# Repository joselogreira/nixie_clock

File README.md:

# **The Nixie Tube Clock** by [Nuvitron]

![alt text][clock_pcb]

At Nuvitron, I led the electronics development of The Nixie Clock hardware included in some of their models. This repository starts from the production version of the clock circuit, and includes further improvements in the form of:

- Code refactoring
- Hardware tweaks (pending)

---

## Toolchain:

This project is based on an [ATmega324pb][324pb] MCU from Atmel (now Microchip). The standard AVR toolchain for Ubuntu Linux was used. No bootloader implemented. Not tested under Windows or Mac.

- [avr-gcc] for compiling and building.
- [avr-libc] for AVR libraries.
- [avrdude] for programming, using [usbasp] programmer or alternatively the official [AVR ISP MK2][mk2]

There're many guides on how to install and set-up the toolchain. [Here's one] of many guides available.

***Sidenote:*** The ATmega324pb MCU is NOT supported by default, neither by *AVRdude* nor by *avr-gcc*, thus, a few extra steps need to be performed in order to get this toolchain to work properly. It's just a matter of including some extra files in the proper locatios to fully support the MCU:
* **AVRdude**: it uses a configuration file that includes all MCUs recognized by the program, among other things. Mine is at `/etc/avrdude.conf`. Edit it (with *root* proviledges) and add an entry for the *ATmega324pb*. Use the *ATmega324pa* as an example, which inherits most of the properties from the ATmega324p. The signature for the 324pb is `1e 95 17`. Alternatively, I've added my `avrdude.conf` to the repo, [here][special].
* **avr-gcc**: A device specification file must be included. My path: `/usr/lib/gcc/avr/5.4.0/device-spec/`. The missing file is called `specs-atmega324pb` and I found it in a Windows installation of [Atmel Studio][astudio], the Atmel IDE for Windows. Within this file there's a couple of dependencies pointing to files in the avr-libc path.
* **avr-libc**: Three files are needed. Again, I found them in the Atmel Studio Windows installation path. My paths for these files are:
  * `/usr/lib/avr/include/avr/` must include the file `iom324pb.h`, which is the memory mapping for all MCU peripherals and special registers.
  * `/usr/lib/avr/lib/avr5/` must include `crtatmega324pb.o` and `libatmega324pb.a`.

***Sidenote 2:*** The latest version of Atmel Studio (7.0, at the time of this writting) doesn't include support for the *ATmega324pb* out-of-the-box. Instead, the user must install an additional package to fully support it. It's called *"Device Firmware Pack"*, and it's installed within Atmel Studio in the *"Device Package Manager"* window. Search for ATmega_DFP and install it. Mine was version `1.2.272`. Once installed, the previously mentioned Windows files can be found at:
  * `\<install-path>\Atmel\Studio\7.0\packs\atmel\ATmega_DFP\1.2.272\include\avr\iom324pb.h`
  * `\<install-path>\Atmel\Studio\7.0\packs\atmel\ATmega_DFP\1.2.272\gcc\dev\atmega324pb\avr5\crtatmega324pb.o` and `libatmega324pb.a`
  * `\<install-path>\Atmel\Studio\7.0\packs\atmel\ATmega_DFP\1.2.272\gcc\dev\atmega324pb\device-specs\specs-atmega324pb`

For the sake of completeness, these files are also included [here][special].

---

## Project Folders
- **src**: contains all the code files needed, including library files.
- **special**: contains all *"additional"* files to support the MCU.
- **img**: some images of the project.
- **docs**: GitHub [project page][ppage].
- **output**: not included in the repo. Automatically created once the Make recipe is executed.

---

## Hardware Characteristics:
- MCU: ATmega324pb 
- (pending)

---

## License

Released under the [MIT License][license] - 2020 Jose Logreira

[clock_pcb]: https://raw.githubusercontent.com/joselogreira/nixie_clock/master/img/clock_pcb.png "Nixie Clock Circuit"
[Nuvitron]: <https://nuvitron.com>
[avr-gcc]: <https://www.microchip.com/mplab/avr-support/avr-and-arm-toolchains-c-compilers>
[avr-libc]: <https://www.nongnu.org/avr-libc/user-manual/overview.html>
[avrdude]: <https://www.nongnu.org/avrdude/>
[usbasp]: <https://www.fischl.de/usbasp/>
[Here's one]: <http://maxembedded.com/2015/06/setting-up-avr-gcc-toolchain-on-linux-and-mac-os-x/>
[special]: /special/
[astudio]: https://www.microchip.com/mplab/avr-support/atmel-studio-7
[324pb]: http://ww1.microchip.com/downloads/en/DeviceDoc/40001908A.pdf
[mk2]: http://ww1.microchip.com/downloads/en/DeviceDoc/Atmel-42093-AVR-ISP-mkII_UserGuide.pdf
[license]: /LICENSE
[ppage]: https://joselogreira.github.io/nixie_clock/

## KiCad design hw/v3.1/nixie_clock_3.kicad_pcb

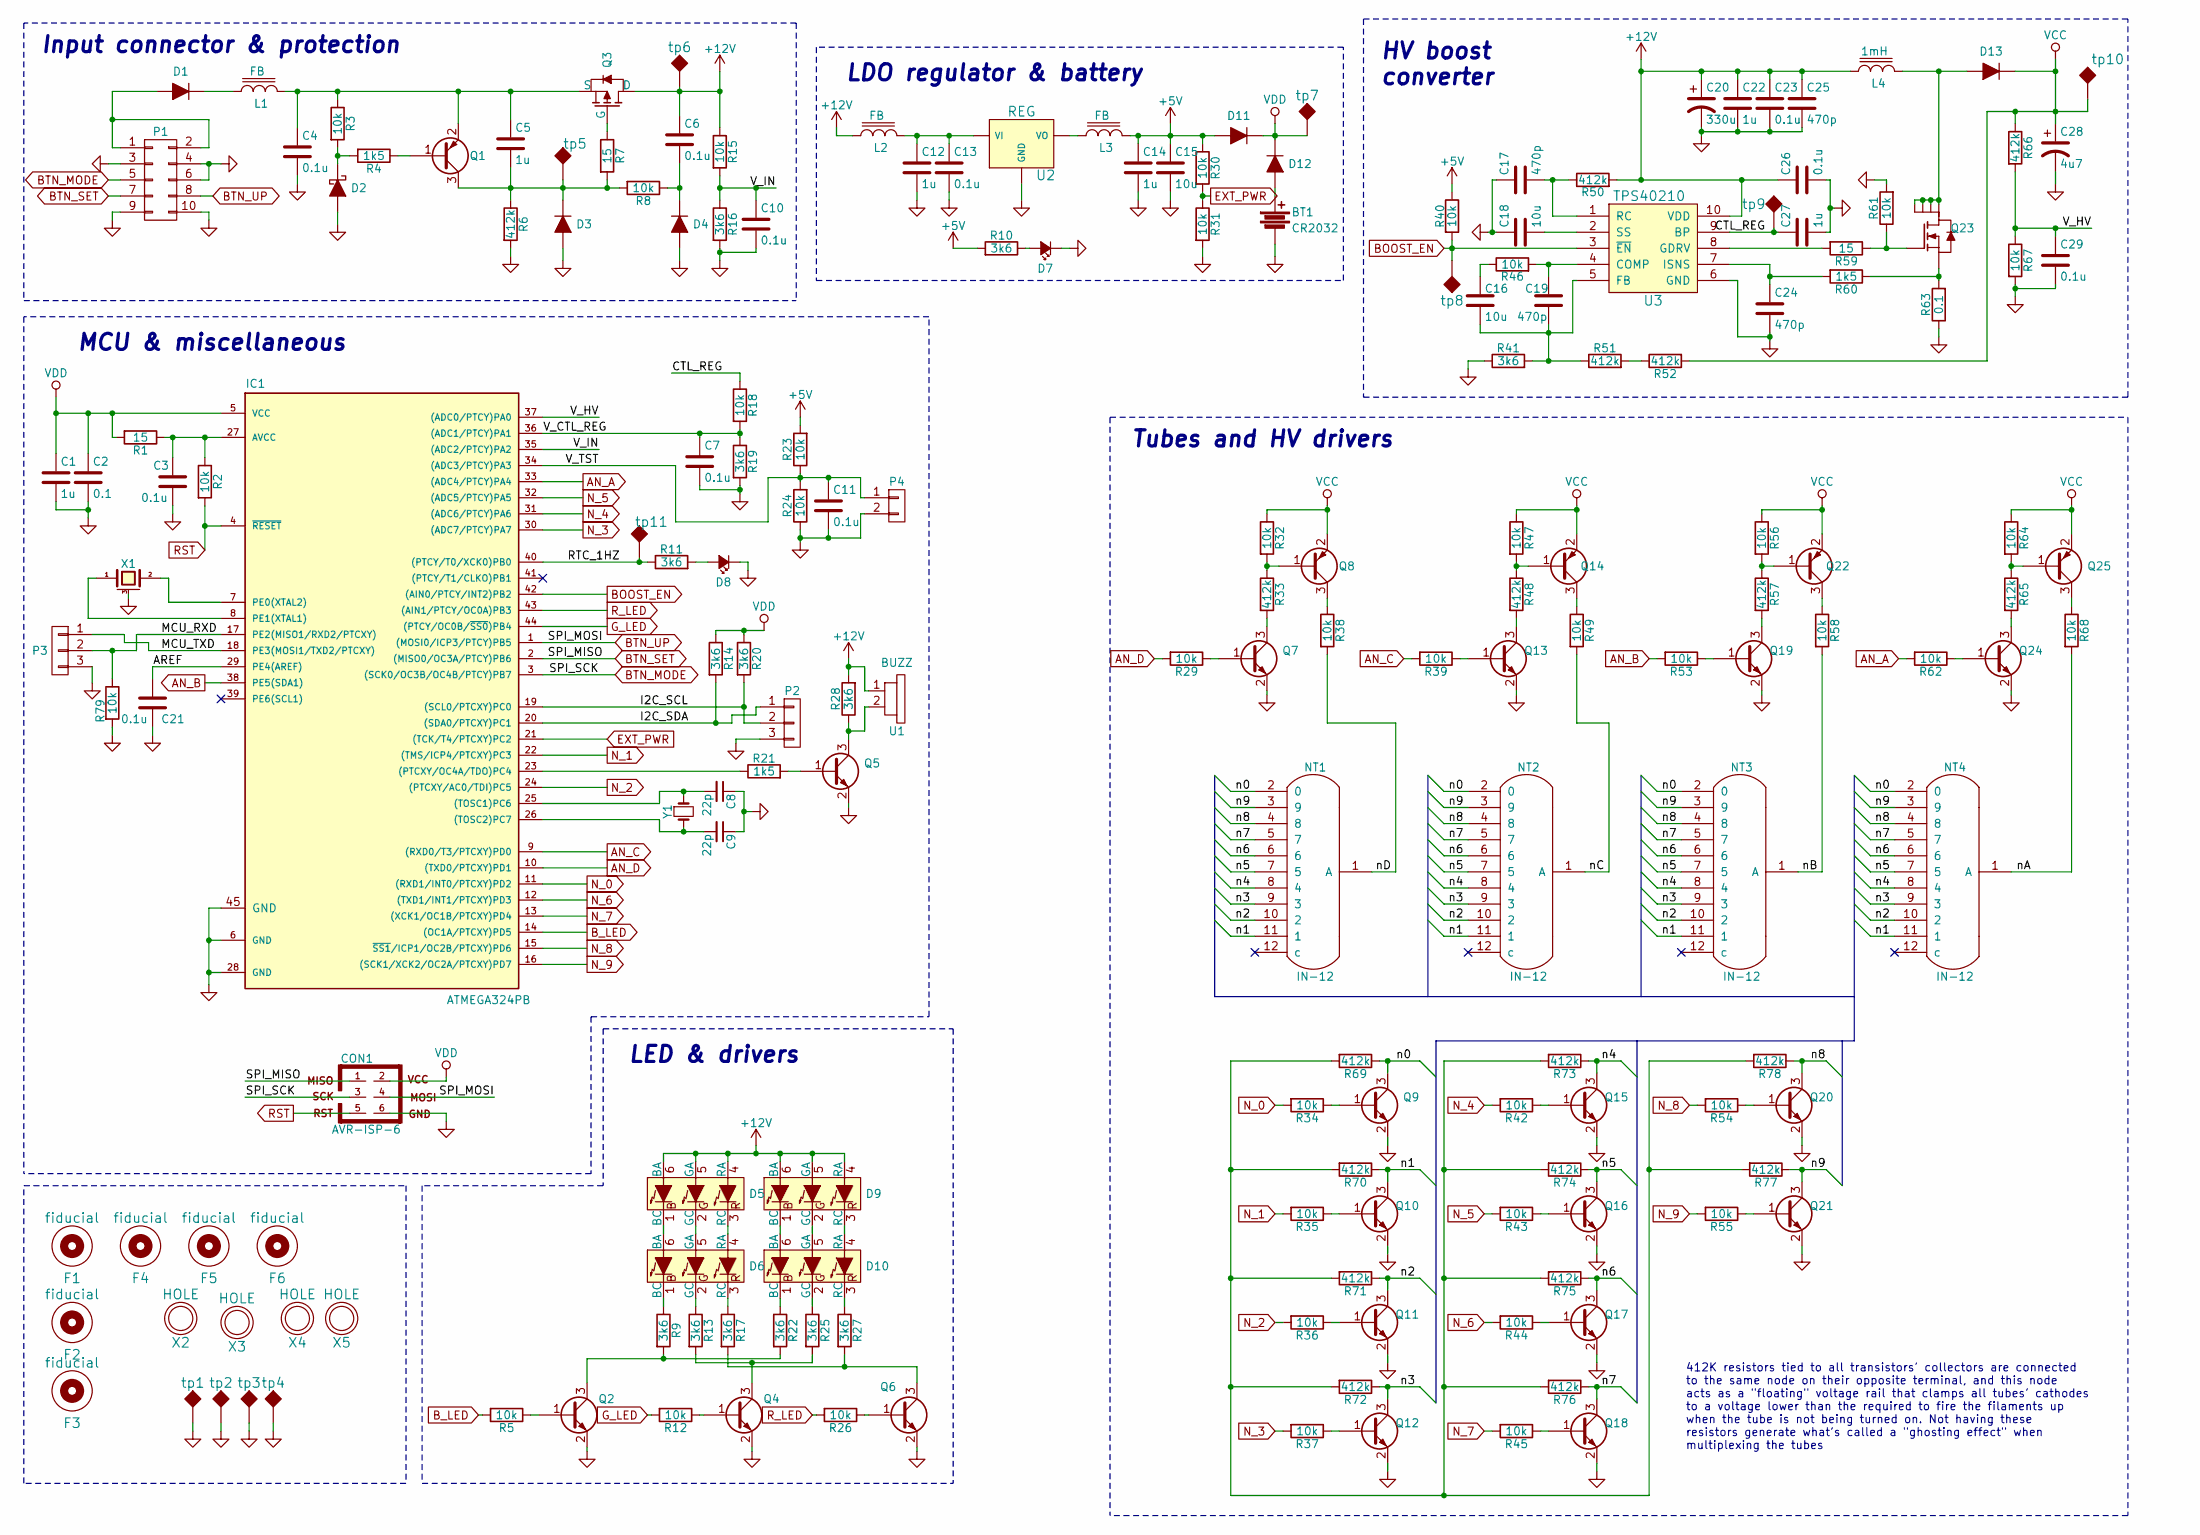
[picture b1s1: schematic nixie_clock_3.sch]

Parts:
BT1: CR2032
C1, C5, C12, C14, C22, C27: 1u; C_0603
C2: 0.1; C_0603
C3, C4, C6, C7, C10, C11, C13, C21, C23, C26, C29: 0.1u; C_0603
C8, C9: 22p; C_0603
C15, C16, C18: 10u; C_0805
C17, C19, C24, C25: 470p; C_0603
C20: 330u; CP_Elec_8x10
C28: 4u7; CP_Elec_8x10
CON1: AVR-ISP-6; ISP_THT_UNPOPULATED
D1, D13: D_ALT; DO-214AC
D2: D_Schottky_ALT; SOD-323
D3, D4, D11, D12: D_ALT; SOD-323
D5, D6, D9, D10: LED_RGB_IND; LED_RGB_PLCC-6-SMALL
D7, D8: Led_Small; D_0603
F1, F2, F3, F4, F5, F6: fiducial; Fiducial_1mm_Dia_2.54mm_Outer_CopperTop
IC1: ATMEGA324PB; QFN-44-1EP_7x7mm_Pitch0.5mm
L1, L2, L3: FB; C_0603
L4: 1mH; IND_1MH_7.3x7.3mm
NT1, NT2, NT3, NT4: IN-12
P1: CONN_02X05; CON_2x5
P2, P3: CONN_01X03; CON_1x3
P4: CONN_01X02; CON_1x2
Q1, Q8, Q14, Q22, Q25: Q_PNP_BEC; SOT-23
Q2, Q4, Q5, Q6, Q7, Q9, Q10, Q11, Q12, Q13, Q15, Q16, Q17, Q18, Q19, Q20, Q21, Q24: Q_NPN_BEC; SOT-23
Q3: Q_PMOS_GSD_; SOT-23
Q23: Q_NMOS_GSD_6; SOT-23-6
R1, R7, R59: 15; C_0603
R2, R3, R5, R8, R12, R15, R18, R23, R24, R26, R29, R30, R31, R32, R34, R35, R36, R37, R38, R39, R40, R42, R43, R44, R45, R46, R47, R49, R53, R54, R55, R56, R58, R61, R62, R64, R67, R68, R79: 10k; C_0603
R4, R21, R60: 1k5; C_0603
R6, R33, R48, R50, R51, R52, R57, R65, R66, R69, R70, R71, R72, R73, R74, R75, R76, R77, R78: 412k; C_0805
R9, R10, R11, R13, R14, R16, R17, R19, R20, R22, R25, R27, R28, R41: 3k6; C_0603
R63: 0.1; C_0603
U1: BUZZ; BUZZ-D12,6_P5
U2: REG; SOT-223
U3: TPS40210; 10-MSOP
X1: CRYSTAL_SMD; CERAMIC_RESONATOR
X2, X3, X4, X5: HOLE; MOUNTING_NPTH_3.2MM
Y1: Crystal_Small; Crystal_3.2x1.5mm
tp1, tp2, tp3, tp4: tp; TestPoint_Pad_3.0x3.0mm
tp5, tp6, tp7, tp8, tp9, tp10, tp11: tp

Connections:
+5V: C14.1, C15.1, D11.2 (A), L3.1, R10.2, R23.2, R30.1, R40.1
+12V: C6.1, C20.1, C22.1, C23.1, C25.1, C26.1, D5.4 (RA), D5.5 (GA), D5.6 (BA), D9.4 (RA), D9.5 (GA), D9.6 (BA), L2.2, L4.2, Q3.3 (D), R15.1, R28.2, R50.2, U1.1, U3.10 (VDD), tp6.1
/AREF: C21.1, IC1.29 (PE4(AREF))
/CTL_REG: C27.1, R18.1, U3.9 (BP), tp9.1
/I2C_SCL: IC1.19 ((SCL0/PTCXY)PC0), P2.2, R20.2
/I2C_SDA: IC1.20 ((SDA0/PTCXY)PC1), P2.1, R14.2
/MCU_RXD: IC1.17 (PE2(MISO1/RXD2/PTCXY)), P3.2, R79.1
/MCU_TXD: IC1.18 (PE3(MOSI1/TXD2/PTCXY)), P3.1
/RTC_1HZ: IC1.40 ((PTCY/T0/XCK0)PB0), R11.1, tp11.1
/V_CTL_REG: C7.1, IC1.36 ((ADC1/PTCY)PA1), R18.2, R19.1
/V_HV: C29.1, IC1.37 ((ADC0/PTCY)PA0), R66.2, R67.1
/V_IN: C10.1, IC1.35 ((ADC2/PTCY)PA2), R15.2, R16.1
/V_TST: C11.1, IC1.34 ((ADC3/PTCY)PA3), P4.1, R23.1, R24.2
/n0: NT1.2 (0), NT2.2 (0), NT3.2 (0), NT4.2 (0), Q9.3 (C), R69.1
/n1: NT1.11 (1), NT2.11 (1), NT3.11 (1), NT4.11 (1), Q10.3 (C), R70.1
/n2: NT1.10 (2), NT2.10 (2), NT3.10 (2), NT4.10 (2), Q11.3 (C), R71.1
/n3: NT1.9 (3), NT2.9 (3), NT3.9 (3), NT4.9 (3), Q12.3 (C), R72.1
/n4: NT1.8 (4), NT2.8 (4), NT3.8 (4), NT4.8 (4), Q15.3 (C), R73.1
/n5: NT1.7 (5), NT2.7 (5), NT3.7 (5), NT4.7 (5), Q16.3 (C), R74.1
/n6: NT1.6, NT2.6, NT3.6, NT4.6, Q17.3 (C), R75.1
/n7: NT1.5 (7), NT2.5 (7), NT3.5 (7), NT4.5 (7), Q18.3 (C), R76.1
/n8: NT1.4 (8), NT2.4 (8), NT3.4 (8), NT4.4 (8), Q20.3 (C), R78.1
/n9: NT1.3 (9), NT2.3 (9), NT3.3 (9), NT4.3 (9), Q21.3 (C), R77.1
/nA: NT4.1 (A), R68.2
/nB: NT3.1 (A), R58.2
/nC: NT2.1 (A), R49.2
/nD: NT1.1 (A), R38.2
AN_A: IC1.33 ((ADC4/PTCY)PA4), R62.2
AN_B: IC1.38 (PE5(SDA1)), R53.2
AN_C: IC1.9 ((RXD0/T3/PTCXY)PD0), R39.2
AN_D: IC1.10 ((TXD0/PTCXY)PD1), R29.2
BOOST_EN: IC1.42 ((AIN0/PTCY/INT2)PB2), R40.2, U3.3 (~EN), tp8.1
BTN_MODE: CON1.3, IC1.3 ((SCK0/OC3B/OC4B/PTCY)PB7), P1.5
BTN_SET: CON1.1, IC1.2 ((MISO0/OC3A/PTCY)PB6), P1.7
BTN_UP: CON1.4, IC1.1 ((MOSI0/ICP3/PTCY)PB5), P1.8
B_LED: IC1.14 ((OC1A/PTCXY)PD5), R5.2
EXT_PWR: IC1.21 ((TCK/T4/PTCXY)PC2), R30.2, R31.1
GND: BT1.2, C1.2, C2.2, C3.2, C4.2, C7.2, C8.1, C9.1, C10.2, C11.2, C12.2, C13.2, C14.2, C15.2, C17.1, C18.1, C20.2, C21.2, C22.2, C23.2, C24.2, C25.2, C26.2, C27.2, C28.2, C29.2, CON1.6, D2.2 (A), D3.2 (A), D4.2 (A), D7.1 (K), D8.1 (K), IC1.6 (GND), IC1.28 (GND), IC1.45 (GND), P1.3, P1.4, P1.6, P1.9, P1.10, P2.3, P3.3, P4.2, Q2.2 (E), Q4.2 (E), Q5.2 (E), Q6.2 (E), Q7.2 (E), Q9.2 (E), Q10.2 (E), Q11.2 (E), Q12.2 (E), Q13.2 (E), Q15.2 (E), Q16.2 (E), Q17.2 (E), Q18.2 (E), Q19.2 (E), Q20.2 (E), Q21.2 (E), Q24.2 (E), R6.2, R16.2, R19.2, R24.1, R31.2, R41.1, R61.2, R63.1, R67.2, R79.2, U2.1 (GND), U3.6 (GND), X1.3 (case), tp1.1, tp2.1, tp3.1, tp4.1
G_LED: IC1.44 ((PTCY/OC0B/~SS0~)PB4), R12.2
N_0: IC1.11 ((RXD1/INT0/PTCXY)PD2), R34.2
N_1: IC1.22 ((TMS/ICP4/PTCXY)PC3), R35.2
N_2: IC1.24 ((PTCXY/AC0/TDI)PC5), R36.2
N_3: IC1.30 ((ADC7/PTCY)PA7), R37.2
N_4: IC1.31 ((ADC6/PTCY)PA6), R42.2
N_5: IC1.32 ((ADC5/PTCY)PA5), R43.2
N_6: IC1.12 ((TXD1/INT1/PTCXY)PD3), R44.2
N_7: IC1.13 ((XCK1/OC1B/PTCXY)PD4), R45.2
N_8: IC1.15 (~SS1~/ICP1/OC2B/PTCXY)PD6), R54.2
N_9: IC1.16 ((SCK1/XCK2/OC2A/PTCXY)PD7), R55.2
unnamed: BT1.1, D12.2 (A)
unnamed: C3.1, IC1.27 (AVCC), R1.1, R2.1
unnamed: C4.1, C5.1, L1.1, Q1.2 (E), Q3.2 (S), R3.1
unnamed: C5.2, D3.1 (K), Q1.3 (C), R6.1, R7.2, R8.2, tp5.1
unnamed: C6.2, D4.1 (K), R8.1
unnamed: C8.2, IC1.25 ((TOSC1)PC6), Y1.1
unnamed: C9.2, IC1.26 ((TOSC2)PC7), Y1.2
unnamed: C12.1, C13.1, L2.1, U2.3 (VI)
unnamed: C16.1, R46.1
unnamed: C16.2, C19.2, R41.2, R51.1, U3.5 (FB)
unnamed: C17.2, R50.1, U3.1 (RC)
unnamed: C18.2, U3.2 (SS)
unnamed: C19.1, R46.2, U3.4 (COMP)
unnamed: C24.1, R60.2, U3.7 (ISNS)
unnamed: D1.1 (K), L1.2
unnamed: D1.2 (A), P1.1, P1.2
unnamed: D2.1 (K), R3.2, R4.2
unnamed: D5.1 (BC), D6.6 (BA)
unnamed: D5.2 (GC), D6.5 (GA)
unnamed: D5.3 (RC), D6.4 (RA)
unnamed: D6.1 (BC), R9.1
unnamed: D6.2 (GC), R13.1
unnamed: D6.3 (RC), R17.1
unnamed: D7.2 (A), R10.1
unnamed: D8.2 (A), R11.2
unnamed: D10.1 (BC), R22.1
unnamed: D10.2 (GC), R25.1
unnamed: D10.3 (RC), R27.1
unnamed: D9.3 (RC), D10.4 (RA)
unnamed: D9.2 (GC), D10.5 (GA)
unnamed: D9.1 (BC), D10.6 (BA)
unnamed: D13.2 (A), L4.1, Q23.1, Q23.2 (D), Q23.5, Q23.6
unnamed: IC1.7 (PE0(XTAL2)), X1.2
unnamed: IC1.8 (PE1(XTAL1)), X1.1
unnamed: IC1.23 ((PTCXY/OC4A/TDO)PC4), R21.1
unnamed: L3.2, U2.2 (VO)
unnamed: Q1.1 (B), R4.1
unnamed: Q2.1 (B), R5.1
unnamed: Q2.3 (C), R9.2, R22.2
unnamed: Q3.1 (G), R7.1
unnamed: Q4.1 (B), R12.1
unnamed: Q4.3 (C), R13.2, R25.2
unnamed: Q5.1 (B), R21.2
unnamed: Q5.3 (C), R28.1, U1.2
unnamed: Q6.1 (B), R26.1
unnamed: Q6.3 (C), R17.2, R27.2
unnamed: Q7.1 (B), R29.1
unnamed: Q7.3 (C), R33.2
unnamed: Q8.1 (B), R32.2, R33.1
unnamed: Q8.3 (C), R38.1
unnamed: Q9.1 (B), R34.1
unnamed: Q10.1 (B), R35.1
unnamed: Q11.1 (B), R36.1
unnamed: Q12.1 (B), R37.1
unnamed: Q13.1 (B), R39.1
unnamed: Q13.3 (C), R48.2
unnamed: Q14.1 (B), R47.2, R48.1
unnamed: Q14.3 (C), R49.1
unnamed: Q15.1 (B), R42.1
unnamed: Q16.1 (B), R43.1
unnamed: Q17.1 (B), R44.1
unnamed: Q18.1 (B), R45.1
unnamed: Q19.1 (B), R53.1
unnamed: Q19.3 (C), R57.2
unnamed: Q20.1 (B), R54.1
unnamed: Q21.1 (B), R55.1
unnamed: Q22.1 (B), R56.2, R57.1
unnamed: Q22.3 (C), R58.1
unnamed: Q23.3 (G), R59.1, R61.1
unnamed: Q23.4 (S), R60.1, R63.2
unnamed: Q24.1 (B), R62.1
unnamed: Q24.3 (C), R65.2
unnamed: Q25.1 (B), R64.2, R65.1
unnamed: Q25.3 (C), R68.1
unnamed: R51.2, R52.1
unnamed: R59.2, U3.8 (GDRV)
unnamed: R69.2, R70.2, R71.2, R72.2, R73.2, R74.2, R75.2, R76.2, R77.2, R78.2
RST: CON1.5, IC1.4 (~RESET), R2.2
R_LED: IC1.43 ((AIN1/PTCY/OC0A)PB3), R26.2
VCC: C28.1, D13.1 (K), Q8.2 (E), Q14.2 (E), Q22.2 (E), Q25.2 (E), R32.1, R47.1, R52.2, R56.1, R64.1, R66.1, tp10.1
VDD: C1.1, C2.1, CON1.2, D11.1 (K), D12.1 (K), IC1.5 (VCC), R1.2, R14.1, R20.1, tp7.1

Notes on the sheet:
Input connector & protection
MCU & miscellaneous
HV boost converter
LDO regulator & battery
Tubes and HV drivers
LED & drivers
412K resistors tied to all transistors' collectors are connected to the same node on their opposite terminal, and this node acts as a "floating" voltage rail that clamps all tubes' cathodes to a voltage lower than the required to fire the filaments up when the tube is not being turned on. Not havin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

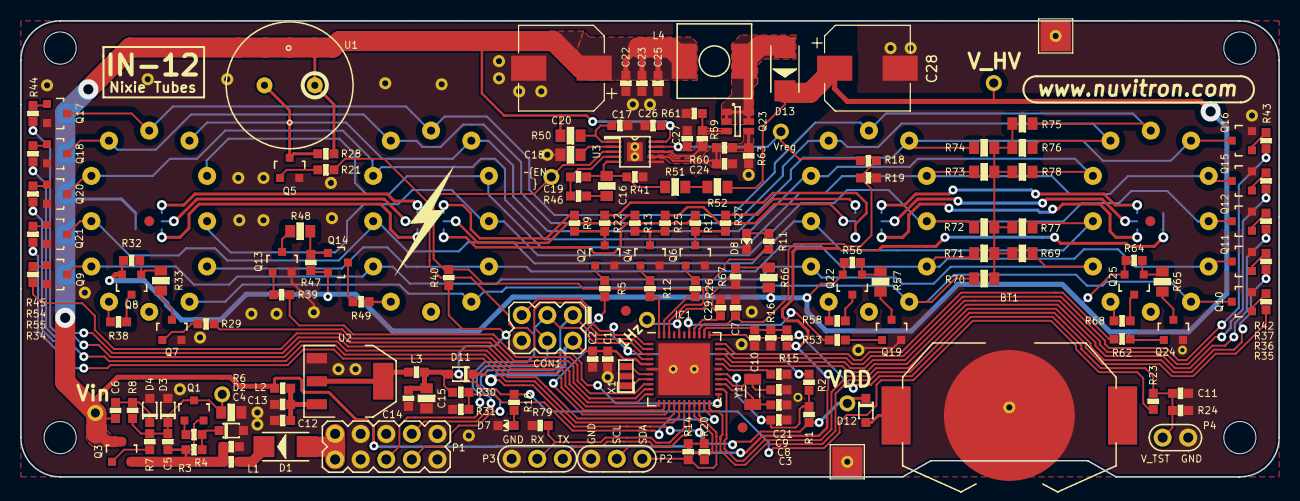
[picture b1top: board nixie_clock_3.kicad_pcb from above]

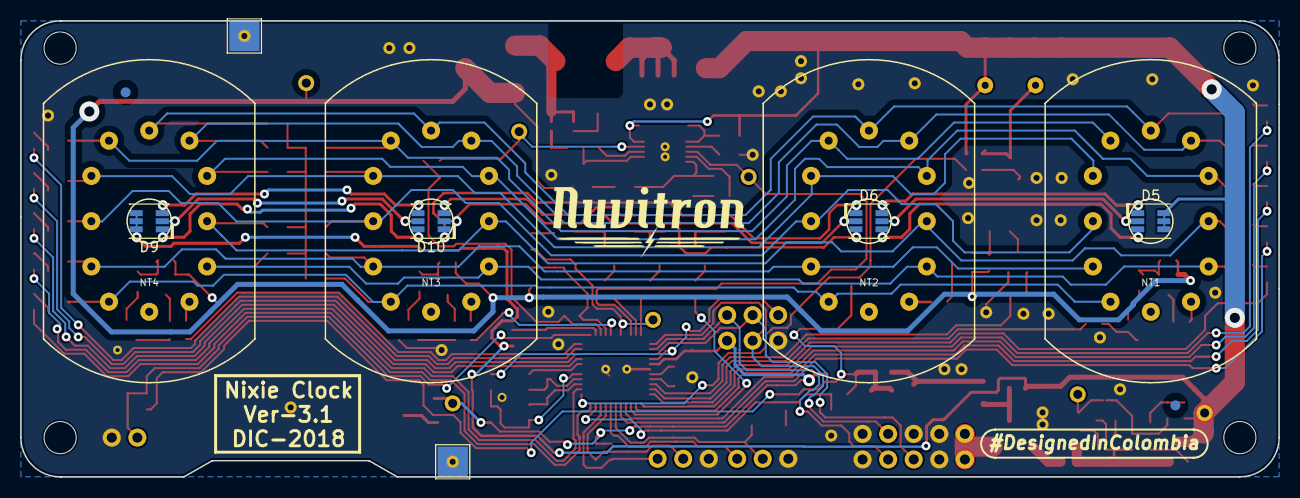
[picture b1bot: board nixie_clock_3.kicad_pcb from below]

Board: 2 copper layers, 125.0 x 45.3 mm, 187 parts (12 on the bottom side), 130 nets.

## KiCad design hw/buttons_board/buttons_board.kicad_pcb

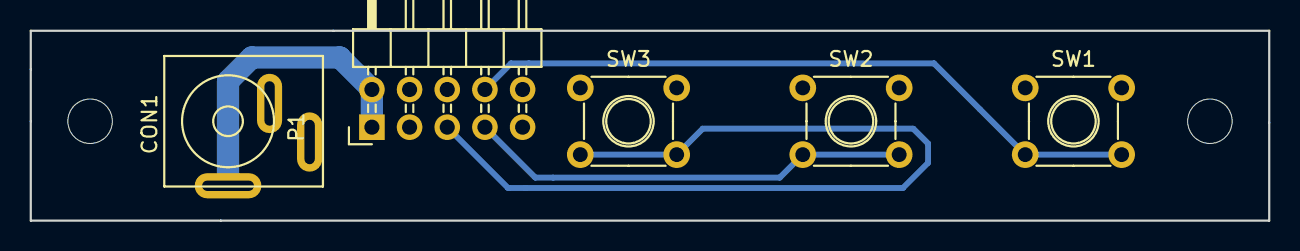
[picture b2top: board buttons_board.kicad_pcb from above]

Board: 2 copper layers, 83.5 x 12.8 mm, 7 parts (0 on the bottom side), 5 nets.

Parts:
CON1: BARREL_JACK; CON_PWR_JACK_5.5x2mm
P1: CONN_02X05; Pin_Header_Angled_2x05
SW1: UP; SW_SPST_THT_6mm
SW2: SET; SW_SPST_THT_6mm
SW3: MODE; SW_SPST_THT_6mm
X1, X2: HOLE; MountingHole_3-5mm

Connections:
GND: CON1.2, CON1.3, P1.3, P1.4, P1.6, SW1.3, SW1.4, SW2.3, SW2.4, SW3.3, SW3.4
unnamed: CON1.1, P1.1, P1.2
unnamed: P1.5, SW3.1, SW3.2
unnamed: P1.7, SW2.1, SW2.2
unnamed: P1.8, SW1.1, SW1.2

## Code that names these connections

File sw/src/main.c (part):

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
    /*
    * Power source check:
    * Look for EXT_PWR pin. If there's an external power adapter connected,
    * Initialize RTC, enable Boost and all other peripherals. Run system.
    * If no voltage in EXT_PWR, it means that battery has been connected first.
    * In that case, do nothing and go to sleep.
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
    /*
    * Production Test Enabled?
    * Use the ADC to sense the V_TST pin. If it is short-circuited, it means
    * that the production test must be launched, and a serial communication
    * link will be estabished with a PC using the UART.
    */
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* adapter connection.
* - When buttons are pressed, btnXYZ.query flag is set and the buttons are
*   polled to determine its state.
* - When EXT_PWR pin triggers the ISR, the power adapter was either removed
*   or plugged. Thus, check EXT_PWR level and decide whether going to sleep
*   or keep normal execution.
*/
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/*===========================================================================*/
/* 
* buttons     
* BTN_X       - PB5 - PCINT13 | -> PCI1
* BTN_Y       - PB6 - PCINT14 | -> PCI1
* BTN_Z       - PB7 - PCINT15 | -> PCI1 
*/
ISR(PCINT1_vect)
{
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/* 
* External power
* if external power is removed, enter in power save mode 
* EXT_PWR     - PC2 - PCINT18  | -> PCI2
*/
ISR(PCINT2_vect)
{
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
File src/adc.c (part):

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/* 
* ADC nominal voltages:
*/
#define V_HV  			((float) 3.794)	// nominal 160V
#define V_HV_OFF		((float) 0.273)	// nominal 11.5V
#define V_CTL_REG 		((float) 2.12)	// nominal 8V
#define V_CTL_REG_OFF 	((float) 0.0)	// nominal 0V
#define V_IN 			((float) 3.01)	// nominal 11.4V
#define V_REF 			((float) 1.1)	// nominal 1.1V
#define V_DD 			((float) 4.3)	// nominal MCU voltage v_dd

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
/*===========================================================================*/
/*
* Checks V_TST pin 3 times. If any of the 3 measurements gives a voltage
* greater than (approximately) 0.5V, it returns FALSE.
* In other words, all 3 measurements should be below 0.5V to return TRUE
*/
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		v_ctl_reg.val_min = (uint16_t)(((float)v_ctl_reg.val_nom) * 0.85);
		v_ctl_reg.val_max = (uint16_t)(((float)v_ctl_reg.val_nom) * 1.15);
	} else {
		v_ctl_reg.val_nom = 0;
		v_ctl_reg.val_min = 0;
		v_ctl_reg.val_max = 25;		// 0.1V
	}

	v_in.val_nom = (uint16_t)((V_IN / v_dd) * 1023.0);
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
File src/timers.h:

/**
 * @file timers.h
 * @brief Timer counter configurations
 *
 * @author Jose Logreira
 * @date 15.05.2018
 *
 */

#ifndef TIMERS_H
#define TIMERS_H

/******************************************************************************
*******************	I N C L U D E   D E P E N D E N C I E S	*******************
******************************************************************************/

#include "config.h"

#include <stdint.h>

/******************************************************************************
***************** S T R U C T U R E   D E C L A R A T I O N S *****************
******************************************************************************/

typedef volatile struct {
    uint8_t mode;
    uint8_t d1;
    uint8_t d2;
    uint8_t d3;
    uint8_t d4;
    uint8_t set;
    uint8_t fade_level[4];
} display_s;

extern display_s display;

/******************************************************************************
******************* C O N S T A N T   D E F I N I T I O N S *******************
******************************************************************************/

// LED Register Counters 
#define R_LED			OCR0A
#define G_LED			OCR0B
#define B_LED			OCR1A

/******************************************************************************
******************** F U N C T I O N   P R O T O T Y P E S ********************
******************************************************************************/

void display_init(void);

void timer_rtc_set(uint8_t state);

void timer_base_init(void);
void timer_buzzer_init(void);
void timer_leds_init(void);

void timer_base_set(uint8_t state);
void timer_buzzer_set(uint8_t state, uint16_t note);
void timer_leds_set(uint8_t state, uint8_t r, uint8_t g, uint8_t b);

#endif	/* TIMERS_H */

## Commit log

2020-06-10 First Commit:
    Nuvitron Code - This is the Nuvitron working code. From here, the
    code will be modified/refactored for better presentation
2020-06-10 gitignore new filetypes
2020-06-10 gitignore modified
2020-06-10 Added readme documentation
2020-06-10 readme corrected
2020-06-10 added image
2020-06-10 added image path
2020-06-10 break point for code refactoring
2020-06-10 First round of code refactoring
    Some decissions: Won't change the general code structure.
    It'll remain as-is just to have it as a good future reference.
    Besides, the code is pretty well documented.
2020-06-10 Added Jekyl Project Page Template
2020-06-10 Bump nokogiri from 1.10.5 to 1.10.9 in /docs
    Bumps [nokogiri](https://github.com/sparklemotion/nokogiri) from 1.10.5 to 1.10.9.
    - [Release notes](https://github.com/sparklemotion/nokogiri/releases)
    - [Changelog](https://github.com/sparklemotion/nokogiri/blob/master/CHANGELOG.md)
    - [Commits](https://github.com/sparklemotion/nokogiri/compare/v1.10.5...v1.10.9)
2020-06-10 config.yml changed
2020-06-10 Bump nokogiri from 1.10.5 to 1.10.8 in /docs
    Bumps [nokogiri](https://github.com/sparklemotion/nokogiri) from 1.10.5 to 1.10.8.
    - [Release notes](https://github.com/sparklemotion/nokogiri/releases)
    - [Changelog](https://github.com/sparklemotion/nokogiri/blob/master/CHANGELOG.md)
    - [Commits](https://github.com/sparklemotion/nokogiri/compare/v1.10.5...v1.10.8)
2020-06-11 Main page texts finished
2020-06-11 Getting started added
2020-06-13 By documenting the code base it's notorious that the main loop code is not clear. It's best to include the sei/cli code and buttons routines inside every display state.
    So let's do it from here
2020-06-15 some more code refactoring
2020-06-16 Added documentation, and some code refactoring for buzzer module
2020-06-19 Corrected .h files dependencies
2020-07-01 Added documentation. Added hw designs
2020-07-01 Added YouTube video to Docs pages
2020-07-01 reduced image sizes
2021-05-20 Bump nokogiri from 1.10.9 to 1.11.4 in /docs
    Bumps [nokogiri](https://github.com/sparklemotion/nokogiri) from 1.10.9 to 1.11.4.
    - [Release notes](https://github.com/sparklemotion/nokogiri/releases)
    - [Changelog](https://github.com/sparklemotion/nokogiri/blob/main/CHANGELOG.md)
    - [Commits](https://github.com/sparklemotion/nokogiri/compare/v1.10.9...v1.11.4)
2021-07-13 Bump addressable from 2.7.0 to 2.8.0 in /docs
    Bumps [addressable](https://github.com/sporkmonger/addressable) from 2.7.0 to 2.8.0.
    - [Release notes](https://github.com/sporkmonger/addressable/releases)
    - [Changelog](https://github.com/sporkmonger/addressable/blob/main/CHANGELOG.md)
    - [Commits](https://github.com/sporkmonger/addressable/compare/addressable-2.7.0...addressable-2.8.0)
    ---
    updated-dependencies:
2021-09-28 Bump nokogiri from 1.10.9 to 1.12.5 in /docs
    Bumps [nokogiri](https://github.com/sparklemotion/nokogiri) from 1.10.9 to 1.12.5.
    - [Release notes](https://github.com/sparklemotion/nokogiri/releases)
    - [Changelog](https://github.com/sparklemotion/nokogiri/blob/main/CHANGELOG.md)
    - [Commits](https://github.com/sparklemotion/nokogiri/compare/v1.10.9...v1.12.5)
    ---
    updated-dependencies:
2022-02-26 Bump nokogiri from 1.10.9 to 1.13.2 in /docs
    Bumps [nokogiri](https://github.com/sparklemotion/nokogiri) from 1.10.9 to 1.13.2.
    - [Release notes](https://github.com/sparklemotion/nokogiri/releases)
    - [Changelog](https://github.com/sparklemotion/nokogiri/blob/main/CHANGELOG.md)
    - [Commits](https://github.com/sparklemotion/nokogiri/compare/v1.10.9...v1.13.2)
    ---
    updated-dependencies:
2022-04-12 Bump nokogiri from 1.10.9 to 1.13.4 in /docs
    Bumps [nokogiri](https://github.com/sparklemotion/nokogiri) from 1.10.9 to 1.13.4.
    - [Release notes](https://github.com/sparklemotion/nokogiri/releases)
    - [Changelog](https://github.com/sparklemotion/nokogiri/blob/v1.13.4/CHANGELOG.md)
    - [Commits](https://github.com/sparklemotion/nokogiri/compare/v1.10.9...v1.13.4)
    ---
    updated-dependencies:
2022-05-19 Bump nokogiri from 1.10.9 to 1.13.5 in /docs
    Bumps [nokogiri](https://github.com/sparklemotion/nokogiri) from 1.10.9 to 1.13.5.
    - [Release notes](https://github.com/sparklemotion/nokogiri/releases)
    - [Changelog](https://github.com/sparklemotion/nokogiri/blob/main/CHANGELOG.md)
    - [Commits](https://github.com/sparklemotion/nokogiri/compare/v1.10.9...v1.13.5)
    ---
    updated-dependencies:
2022-05-24 Bump nokogiri from 1.10.9 to 1.13.6 in /docs
    Bumps [nokogiri](https://github.com/sparklemotion/nokogiri) from 1.10.9 to 1.13.6.
    - [Release notes](https://github.com/sparklemotion/nokogiri/releases)
    - [Changelog](https://github.com/sparklemotion/nokogiri/blob/main/CHANGELOG.md)
    - [Commits](https://github.com/sparklemotion/nokogiri/compare/v1.10.9...v1.13.6)
    ---
    updated-dependencies:
2022-07-22 Bump tzinfo from 1.2.7 to 1.2.10 in /docs
    Bumps [tzinfo](https://github.com/tzinfo/tzinfo) from 1.2.7 to 1.2.10.
    - [Release notes](https://github.com/tzinfo/tzinfo/releases)
    - [Changelog](https://github.com/tzinfo/tzinfo/blob/master/CHANGES.md)
    - [Commits](https://github.com/tzinfo/tzinfo/compare/v1.2.7...v1.2.10)
    ---
    updated-dependencies:
2022-10-06 Bump addressable from 2.7.0 to 2.8.1 in /docs
    Bumps [addressable](https://github.com/sporkmonger/addressable) from 2.7.0 to 2.8.1.
    - [Release notes](https://github.com/sporkmonger/addressable/releases)
    - [Changelog](https://github.com/sporkmonger/addressable/blob/main/CHANGELOG.md)
    - [Commits](https://github.com/sporkmonger/addressable/compare/addressable-2.7.0...addressable-2.8.1)
    ---
    updated-dependencies:
2022-10-20 Bump nokogiri from 1.10.9 to 1.13.9 in /docs
    Bumps [nokogiri](https://github.com/sparklemotion/nokogiri) from 1.10.9 to 1.13.9.
    - [Release notes](https://github.com/sparklemotion/nokogiri/releases)
    - [Changelog](https://github.com/sparklemotion/nokogiri/blob/main/CHANGELOG.md)
    - [Commits](https://github.com/sparklemotion/nokogiri/compare/v1.10.9...v1.13.9)
    ---
    updated-dependencies:
2023-01-31 Bump activesupport from 6.0.3.1 to 6.0.6.1 in /docs
    Bumps [activesupport](https://github.com/rails/rails) from 6.0.3.1 to 6.0.6.1.
    - [Release notes](https://github.com/rails/rails/releases)
    - [Changelog](https://github.com/rails/rails/blob/v7.0.4.2/activesupport/CHANGELOG.md)
    - [Commits](https://github.com/rails/rails/compare/v6.0.3.1...v6.0.6.1)
    ---
    updated-dependencies:
2023-04-12 Bump nokogiri from 1.10.9 to 1.14.3 in /docs
    Bumps [nokogiri](https://github.com/sparklemotion/nokogiri) from 1.10.9 to 1.14.3.
    - [Release notes](https://github.com/sparklemotion/nokogiri/releases)
    - [Changelog](https://github.com/sparklemotion/nokogiri/blob/main/CHANGELOG.md)
    - [Commits](https://github.com/sparklemotion/nokogiri/compare/v1.10.9...v1.14.3)
    ---
    updated-dependencies:
